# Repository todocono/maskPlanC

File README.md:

# maskPlanC
This document can work well with the assembly instructions for the face mask hosted at https://drive.google.com/file/d/1PCkjFUZ8gI0-NtIk4xPe1UZWPMF1h7Cg/view?usp=sharing
Designed by Gabriele Ermacora, Yinmiao Li, Momoe Nomoto & Rodolfo Cossovich
This repository uses elements from https://github.com/todocono/tinyworkshop

## Programming 

LED Blink  
What’s under the hood: https://www.arduino.cc/en/uploads/Main/arduino-uno-schematic.pdf  
What “they don’t tell you”: https://cdn.sparkfun.com/assets/c/a/8/e/4/Atmel-42735-8-bit-AVR-Microcontroller-ATmega328-328P_Datasheet.pdf  
Diversity: https://ww1.microchip.com/downloads/en/DeviceDoc/Atmel-2586-AVR-8-bit-Microcontroller-ATtiny25-ATtiny45-ATtiny85_Datasheet.pdf  
How Arduinos are born: https://en.wikipedia.org/wiki/In-system_programming  
Hackers welcome: https://www.arduino.cc/en/tutorial/arduinoISP  
These pins: https://www.instructables.com/id/Program-an-ATtiny-with-Arduino/  
Bypass!!! Capacitor 10uF  
This board: https://raw.githubusercontent.com/damellis/attiny/ide-1.6.x-boards-manager/package_damellis_attiny_index.json  
LED Blink  
8MHz boot loader: LED Blink  
analogWrite  
Stingy Watchdog: https://www.insidegadgets.com/2011/02/05/reduce-attiny-power-consumption-by-sleeping-with-the-watchdog-timer/  

## PCB Design 

CAD Software: https://predictabledesigns.com/pcb-design-software-which-one-is-best/  
Eagle: https://www.autodesk.com/products/eagle/free-download  
Help from Sparkfun: https://learn.sparkfun.com/tutorials/how-to-install-and-setup-eagle  
Help for the help: https://learn.sparkfun.com/tutorials/pcb-basics/all  
ATtiny85 footprint: https://www.snapeda.com/parts/ATTINY85-20PU/Microchip/view-part/  
LEDs & everything else: https://github.com/adafruit/Adafruit-Eagle-Library  
Measure well or measure twice: PRINT!  

## Manufacturing 

Ironing your PCB: https://www.sparkfun.com/news/2116?_ga=2.74353041.282288770.1571127757-1077704488.1567749628  
ProtoMat 43: https://www.lpkfusa.com/products/pcb_prototyping/machines/protomat_s64/  
Exporting circuits -old style-: http://optics.eee.nottingham.ac.uk/eagle/eagle2lpkf_at_eee.html  
Western approach: https://oshpark.com/  
PCB paradise: https://www.jdbpcb.com/

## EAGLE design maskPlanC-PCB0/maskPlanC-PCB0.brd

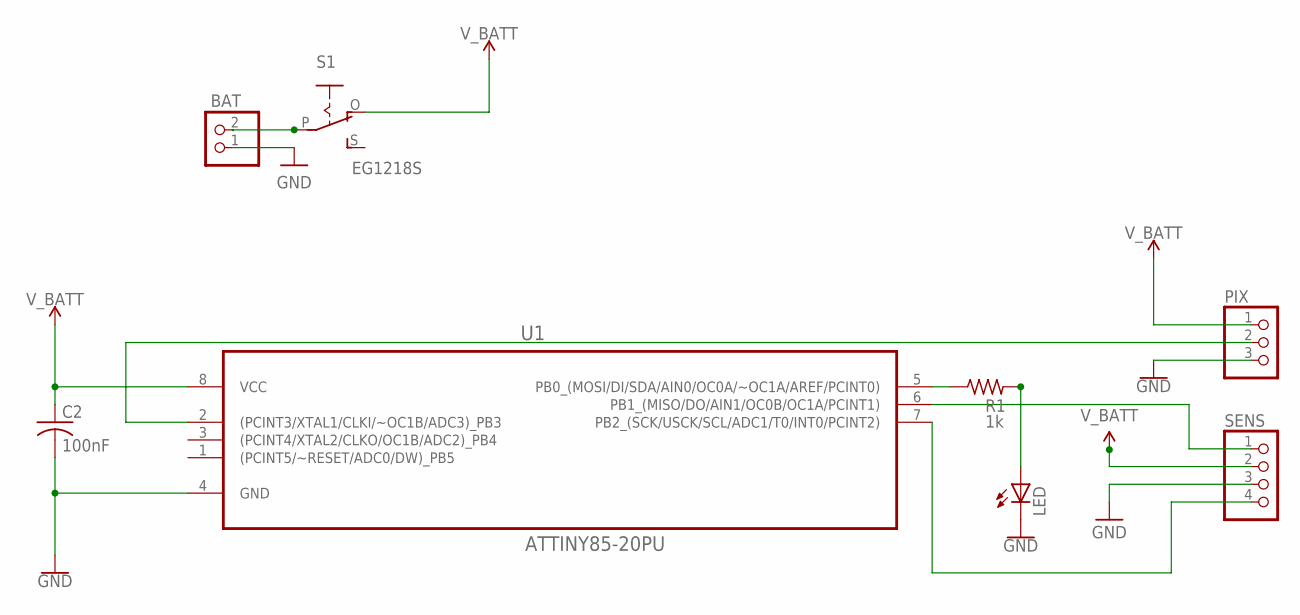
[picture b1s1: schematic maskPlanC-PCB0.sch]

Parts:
BAT: PINHD-1X2; 1X02
C2: 100nF; C050-025X075
LED: LED5MM
PIX: PINHD-1X3; 1X03
R1: 1k; 0204/7
S1: EG1218S; EG1218
SENS: PINHD-1X4; 1X04
U1: ATTINY85-20PU; DIP254P762X533-8

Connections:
GND: BAT.1, C2.2, LED.K (C), PIX.3, SENS.3, U1.4 (GND)
unnamed: SENS.1, U1.6 (PB1_(MISO/DO/AIN1/OC0B/OC1A/PCINT1))
unnamed: LED.A, R1.2
unnamed: BAT.2, S1.P
unnamed: PIX.2, U1.2 ((PCINT3/XTAL1/CLKI/~OC1B/ADC3)_PB3)
unnamed: R1.1, U1.5 (PB0_(MOSI/DI/SDA/AIN0/OC0A/~OC1A/AREF/P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)
unnamed: SENS.4, U1.7 (PB2_(SCK/USCK/SCL/ADC1/T0/INT0/PCINT2))
V_BATT: C2.1, PIX.1, S1.O, SENS.2, U1.8 (VCC)

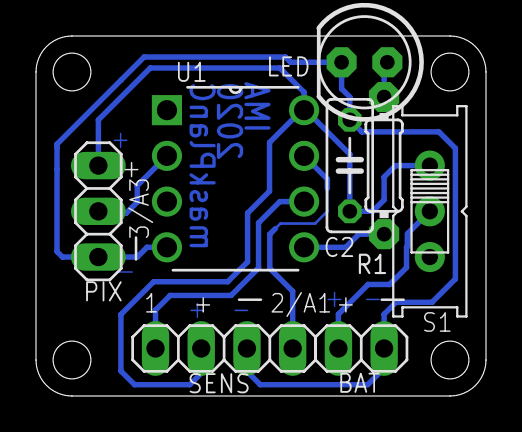
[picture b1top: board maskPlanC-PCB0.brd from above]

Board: 2 copper layers, 25.0 x 20.0 mm, 8 parts (0 on the bottom side), 8 nets.

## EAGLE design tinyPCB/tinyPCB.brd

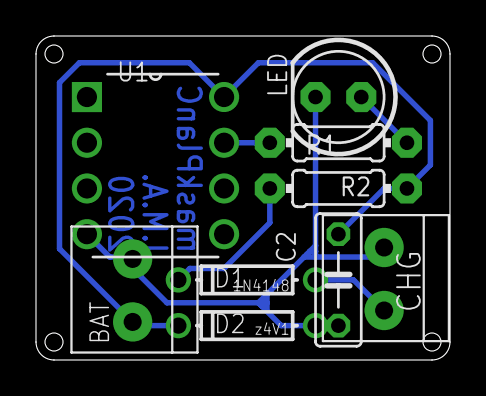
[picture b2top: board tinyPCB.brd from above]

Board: 2 copper layers, 23.0 x 18.0 mm, 9 parts (0 on the bottom side), 6 nets.

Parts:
BAT: 1X2-3.5MM
C2: 100nF; C050-025X075
CHG: 1X2-3.5MM
D1: 1N4148; DO-1N4148
D2: z4V1; DO-1N4148
LED: LED5MM
R1, R2: 1k; 0204/7
U1: ATTINY85-20PU; DIP254P762X533-8

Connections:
GND: BAT.1, C2.2, CHG.1, D2.A, LED.K, U1.4
unnamed: R1.1, U1.7
unnamed: LED.A, R1.2
unnamed: D1.C, R2.1
VCC: CHG.2, D1.A
V_BATT: BAT.2, C2.1, D2.C, R2.2, U1.8

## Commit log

2020-11-30 plan C
2020-11-30 added PCB & software for matrix
2020-11-30 added PCB & software for matrix2
2020-12-01 PCB routed
2020-12-01 CAM v1

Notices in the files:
parts and their libraries:
SparkFun-PowerSymbols: Licensing: Creative Commons ShareAlike 4.0 International - https://creativecommons.org/licenses/by-sa/4.0
